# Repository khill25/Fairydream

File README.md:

# Fairydream
A pico powered, one color LED strip controller

I have a string of Fairy Lights around the permieter of my bedroom and the control unit for it keeps dying. The controller won't work right, dimming stops working... I typically resort to manually plugging and unplugging them but the brightness varies based on random factors and it's just not convenient.

So I built my own controller! PCBs are on order from PCBWay but the prototype using a relay and a voltage regulator to step down the 15v to 5v for the pico is working but the voltage regulator gets so hot that I designed a new pcb.

## Build Instructions
Coming soon... PCBs aren't ordered yet :p

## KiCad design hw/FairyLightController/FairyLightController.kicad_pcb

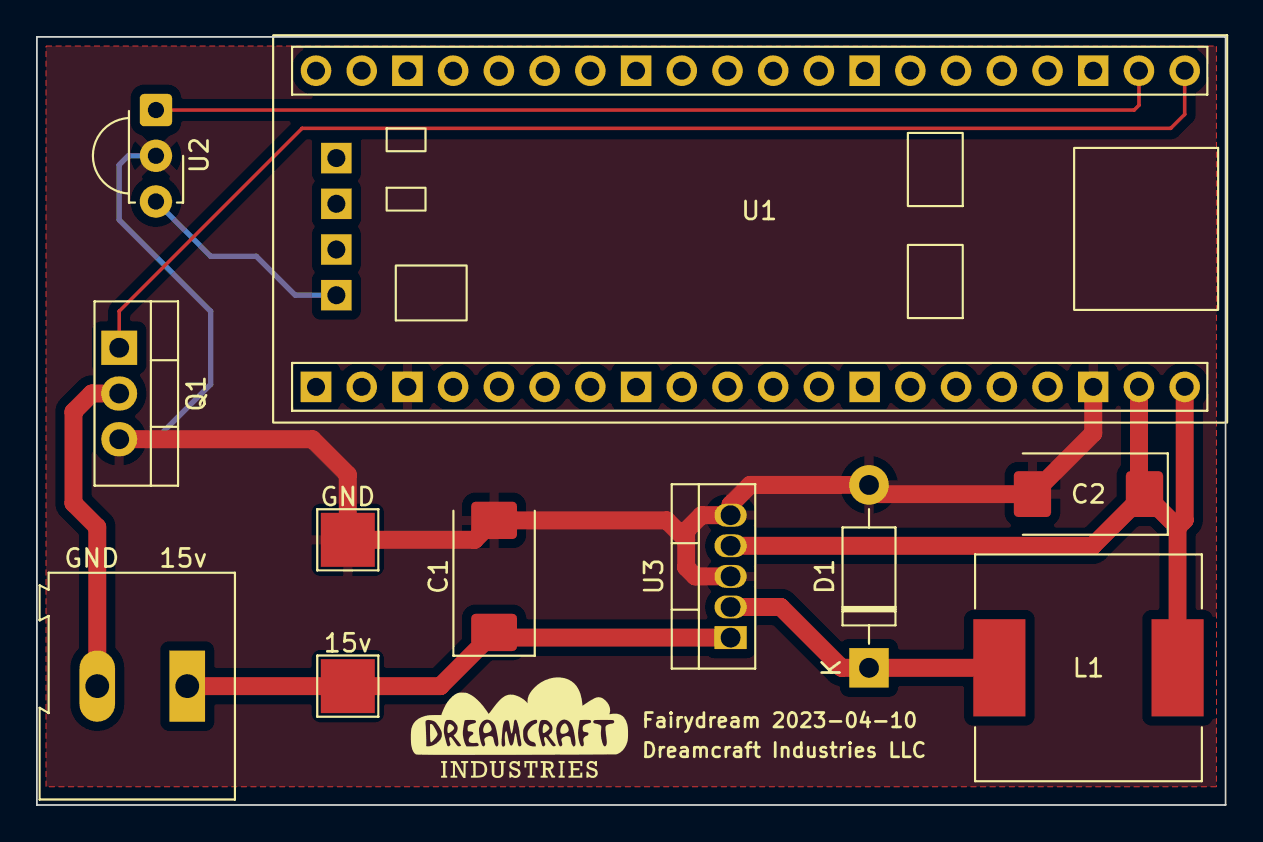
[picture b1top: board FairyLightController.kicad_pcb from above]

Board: 2 copper layers, 66.0 x 42.7 mm, 11 parts (0 on the bottom side), 8 nets.

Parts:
15v: POWER IN; TestPoint_Pad_3.0x3.0mm
C1: 100uf; CP_EIA-7343-30_AVX-N
C2: 330uf; CP_EIA-7343-30_AVX-N
D1: 1N5819; D_DO-41_SOD81_P10.16mm_Horizontal
GND: GND; TestPoint_Pad_3.0x3.0mm
J1: LEDs; TerminalBlock_Altech_AK300-2_P5.00mm
L1: 330uh; L_12x12mm_H6mm
Q1: IRLZ44N; TO-220-3_Vertical
U1: WeAct-RP2040-Pico
U2: TSOP382xx; Vishay_MINICAST-3Pin
U3: LM2575-5.0BT; TO-220-5_Vertical

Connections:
+3V3: U1.37 (3V3), U1.44 (3V3), U2.3 (Vs)
+5V: C2.1, L1.2, U1.39 (VSYS), U1.40 (VBUS), U3.4 (FB)
+15V: 15v.1, C1.1, J1.1, U3.1 (VIN)
/GP0: Q1.1 (G), U1.1 (GP0)
/GP1: U1.2 (GP1), U2.1 (OUT)
GND: C1.2, C2.2, D1.2 (A), GND.1, Q1.3 (S), U1.23 (GND), U1.38 (GND), U2.2 (GND), U3.3 (GND), U3.5 (~ON/OFF)
unnamed: D1.1 (K), L1.1, U3.2 (OUT)
unnamed: J1.2, Q1.2 (D)

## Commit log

2023-04-11 Initial commit, contains v1 pcb and software. The software is currently written to control a relay and will need to be changed once the new boards arrive as we will be controlling a mosfet with pwm.
2023-04-27 Add dimming support and 100-10% brightness values. The LIGHT_LEVEL_MULTIPLIER may need to be changed if 100% (65536) is too bright and causes the lights to mess up.
